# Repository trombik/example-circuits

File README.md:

# Example circuits

Various circuits I find useful.

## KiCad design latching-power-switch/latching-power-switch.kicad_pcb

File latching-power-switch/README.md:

# Latching power switch uses momentary push button

A high-side switch that uses a momentary push button
([Latching power switch uses momentary pushbutton](https://www.edn.com/latching-power-switch-uses-momentary-pushbutton/)).

There are other designs, but I like the design because:

* it uses common components
* it is easy to understand how it works
* quiescent current is zero

## Notes

Make sure polarity of MOSFET is correct.

BS250 has relatively higher Rds(on) (10Ohms @200mA).

Use a bigger MOSFET to increase output current.

Use a series diode in output when the load is inductive.

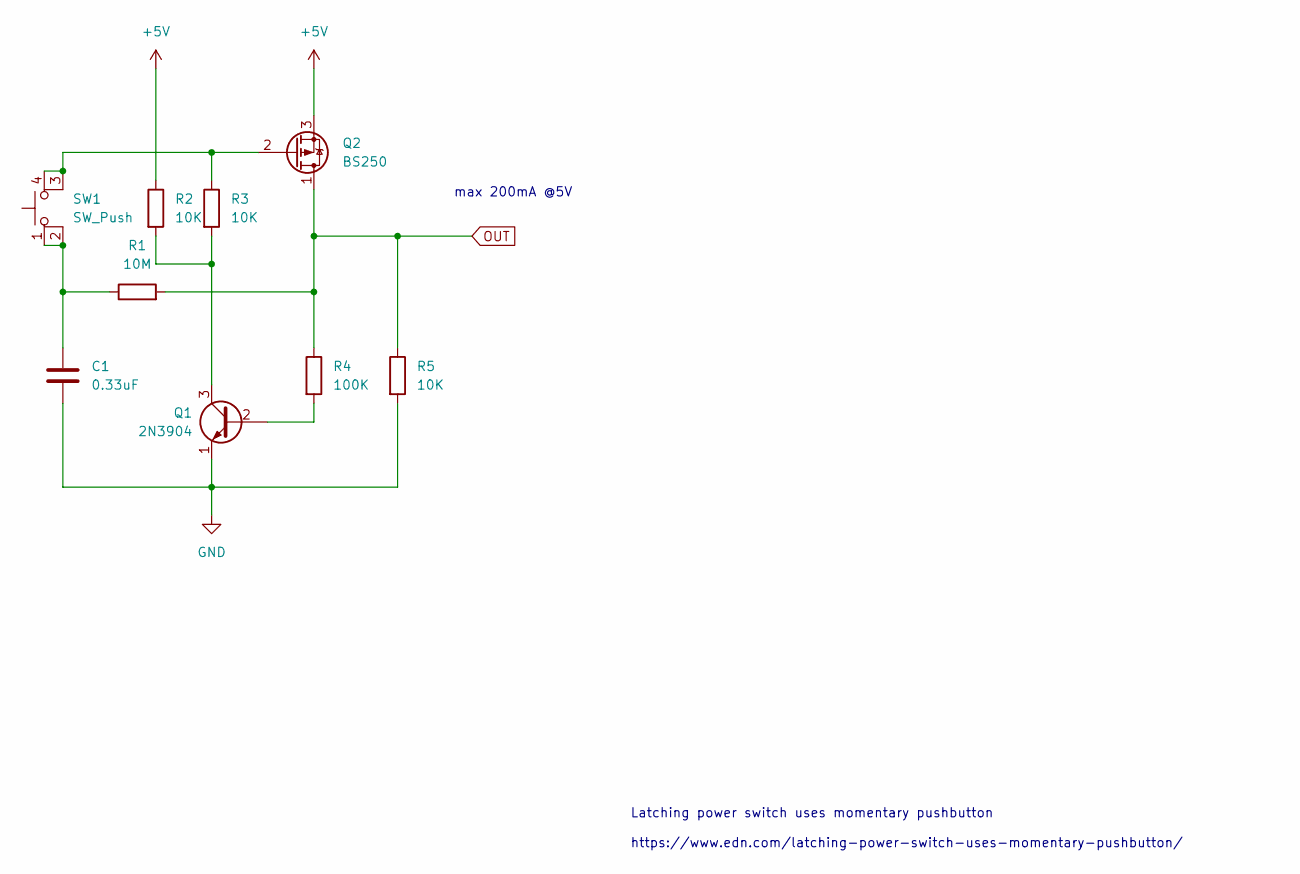
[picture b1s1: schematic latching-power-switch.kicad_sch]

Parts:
C1: 0.33uF; C_Disc_D5.0mm_W2.5mm_P5.00mm
Q1: 2N3904; TO-92_Inline_Wide
Q2: BS250; TO-92_Inline_Wide
R1: 10M; R_Axial_DIN0207_L6.3mm_D2.5mm_P7.62mm_Horizontal
R2: 10K; R_Axial_DIN0207_L6.3mm_D2.5mm_P10.16mm_Horizontal
R3, R5: 10K; R_Axial_DIN0207_L6.3mm_D2.5mm_P7.62mm_Horizontal
R4: 100K; R_Axial_DIN0207_L6.3mm_D2.5mm_P7.62mm_Horizontal
SW1: SW_Push; SW_PUSH_6mm

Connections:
+5V: Q2.3 (S), R2.1
GND: C1.2, Q1.1 (E), R5.2
unnamed: C1.1, R1.1, SW1.1, SW1.2
unnamed: Q1.2 (B), R4.2
unnamed: Q1.3 (C), R2.2, R3.2
unnamed: Q2.2 (G), R3.1, SW1.3 (K), SW1.4 (A)
OUT: Q2.1 (D), R1.2, R4.1, R5.1

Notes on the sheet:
max 200mA @5V
Latching power switch uses momentary pushbutton https://www.edn.com/latching-power-switch-uses-momentary-pushbutton/

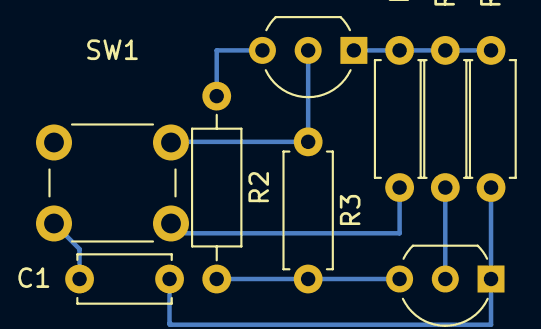
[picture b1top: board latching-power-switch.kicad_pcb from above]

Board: 2 copper layers, 9 parts (0 on the bottom side), 7 nets.

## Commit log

2022-07-18 feat(latching-power-switch): initial import
2022-07-18 feat(latching-power-switch): add SVG file
2022-07-18 update(latching-power-switch): add PCB layout
2022-07-18 chore: ignore fp-info-cache
2022-07-18 doc(latching-power-switch): fix a typo, add why I like it
2022-07-18 doc: embed the schematic into README
2022-07-18 doc: use <img> not <a>
2022-07-18 bugfix: draw backgorund color in schematic
    to support dark mode in browser
2022-07-21 feat: add 555 PWM
2022-07-21 fix a tag
2022-07-21 feat: add 555 timer
2022-07-24 bugfix: resize schematic
2022-07-26 feat: add BJT push-pull
2022-08-09 feat: A continuity checker with a comparator
2022-08-10 doc: add a picture of continuity checker
2022-08-10 feat: add avr-input example
2022-08-10 chore: rename avr-input to avr-input-output
2022-08-10 doc: add kicad project to avr-input-output
2022-08-11 doc: add schmatic to README
2022-08-11 bugfix: fix background in schematic
2022-08-11 doc: document why avr/sfr_defs.h is not icnluded
2022-08-11 doc(avr-input-output): explain the target MCU
2022-08-11 feat(avr-input-output): add upload settings to platformio.ini
2022-08-11 doc: describe what avr-input-output does
2022-08-11 feat(avr-input-output): add attiny13 target
2022-08-11 doc(avr-input-output): mention programmers
2022-08-11 doc(avr-input-output): document pio targets
2022-08-11 feat: add avr-blink example
2022-08-11 bugfix: make schematic scalable
2022-08-11 bugfix: correct CPU clock on ATTiny13
2022-08-12 feat: add transistor as a switch example
2022-08-12 doc: add link to 2N3904 datasheet
2022-08-12 feat: mosfet-switch example
2022-08-12 bugfix: s/>/</
2022-08-13 feat: add RC network
